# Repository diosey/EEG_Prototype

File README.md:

# EEG Prototype — Wireless Brain Activity Acquisition System

A prototype electroencephalograph (EEG) for acquiring and recording the brain's electrical activity, with real-time visualization in both time and frequency domains.

Developed as a degree project at Universidad Politécnica Territorial de Aragua "Federico Brito Figueroa" (Venezuela).

---

## Overview

This project implements a complete EEG acquisition system composed of:

- **Analog front-end**: Low-noise biopotential acquisition circuit with instrumentation amplifier, eighth-order active filter with butterworth topology, non-inverting adder for an offset to adapt the signal to logical level required for ADC and microcontroller, notch filter to mitigate the 60Hz noise 
- **Digital processing**: ESP32 microcontroller with websockets for communication
- **Wireless communication**: WiFi for real-time data streaming
- **Web interface**: Browser-based visualization of EEG signals in time and frequency domains with FIR and IIR digital filters

The system captures brain electrical activity on the ESP32, streams raw 16-bit samples over WebSocket, and applies digital filtering (31-tap FIR with Hamming window, 1st-order IIR, both low-pass and high-pass) in the browser for real-time visualization in the time and frequency domains.

---

## Specifications

| Parameter | Value |
|-----------|-------|
| Signal type | Brain electrical activity (EEG) |
| Channels | 1 |
|Biopotential amplifier | G = 10000 |
| Sampling rate | 430 Hz |
| ADC resolution | 16 bits |
| Microcontroller | ESP32 |
| Digital filters | FIR (31-tap, Hamming) + IIR (1st order) |
| Filter types | Low-pass and high-pass |
| Frequency analysis | Power spectrum (FFT) |
| Communication | WiFi (802.11 b/g/n) |
| Visualization | Web browser (HTML/JavaScript) |
| Firmware language | C |
| Design tool | KiCad |

---

## Design Highlights

- **Analog biopotential amplification**: Circuit based on the AD620 due to its low noise and high CMRR
- **Complete system integration**: Analog acquisition + digital processing + wireless communication + web visualization in a single project.
- **Digital signal processing**: FIR and IIR filters implemented in JavaScript on the client-side, with configurable low-pass and high-pass modes.
- **Frequency-domain analysis**: Real-time power spectrum computed via FFT.
- **Wireless data streaming**: WiFi WebSocket server streams EEG data to any browser.
- **Cross-platform visualization**: Works on PC, tablet, or smartphone without installing any application.
- **Open hardware design**: Full KiCad schematic, PCB, and Gerbers included.

---

## Repository Structure

- `hardware/` — KiCad schematic, PCB, Gerbers, BOM
- `firmware/` — ESP-IDF source project
- `docs/` — Design documentation, calculations, thesis summary

---

## Signal Processing

### FIR Filter
- **Topology**: 31-tap FIR
- **Window**: Hamming
- **Configurations**: Low-pass and high-pass

### IIR Filter
- **Topology**: 1st-order IIR
- **Configurations**: Low-pass and high-pass

### Frequency Analysis
- FFT-based power spectrum
- Real-time display in web interface

---

## Web Interface

The web interface allows visualization of EEG signals from any device with a browser (PC, tablet, smartphone) connected to the same WiFi network.

Features:
- Real-time time-domain plot
- Real-time frequency-domain plot (power spectrum)
- Filter selection (FIR/IIR, LP/HP)

---

## Tools Used

- **KiCad** — Schematic capture, PCB layout
- **ESP-IDF / PlatformIO** — ESP32 firmware development
- **C** — Firmware programming language
- **HTML/CSS/JavaScript** — Web interface

---

## Team

- **David Obregon** 
- **Diosey Lugo** 

**Tutor:** Prof. Carlos Aponte

**Institution:** Universidad Politécnica Territorial de Aragua "Federico Brito Figueroa"
**Date:** April 2026

---

## Author Contact
- **Gmail:** dioseyadolfolugo@gmail.com
- **GitHub:** https://github.com/diosey
- **LinkedIn:** http://www.linkedin.com/in/adolfodiaz01

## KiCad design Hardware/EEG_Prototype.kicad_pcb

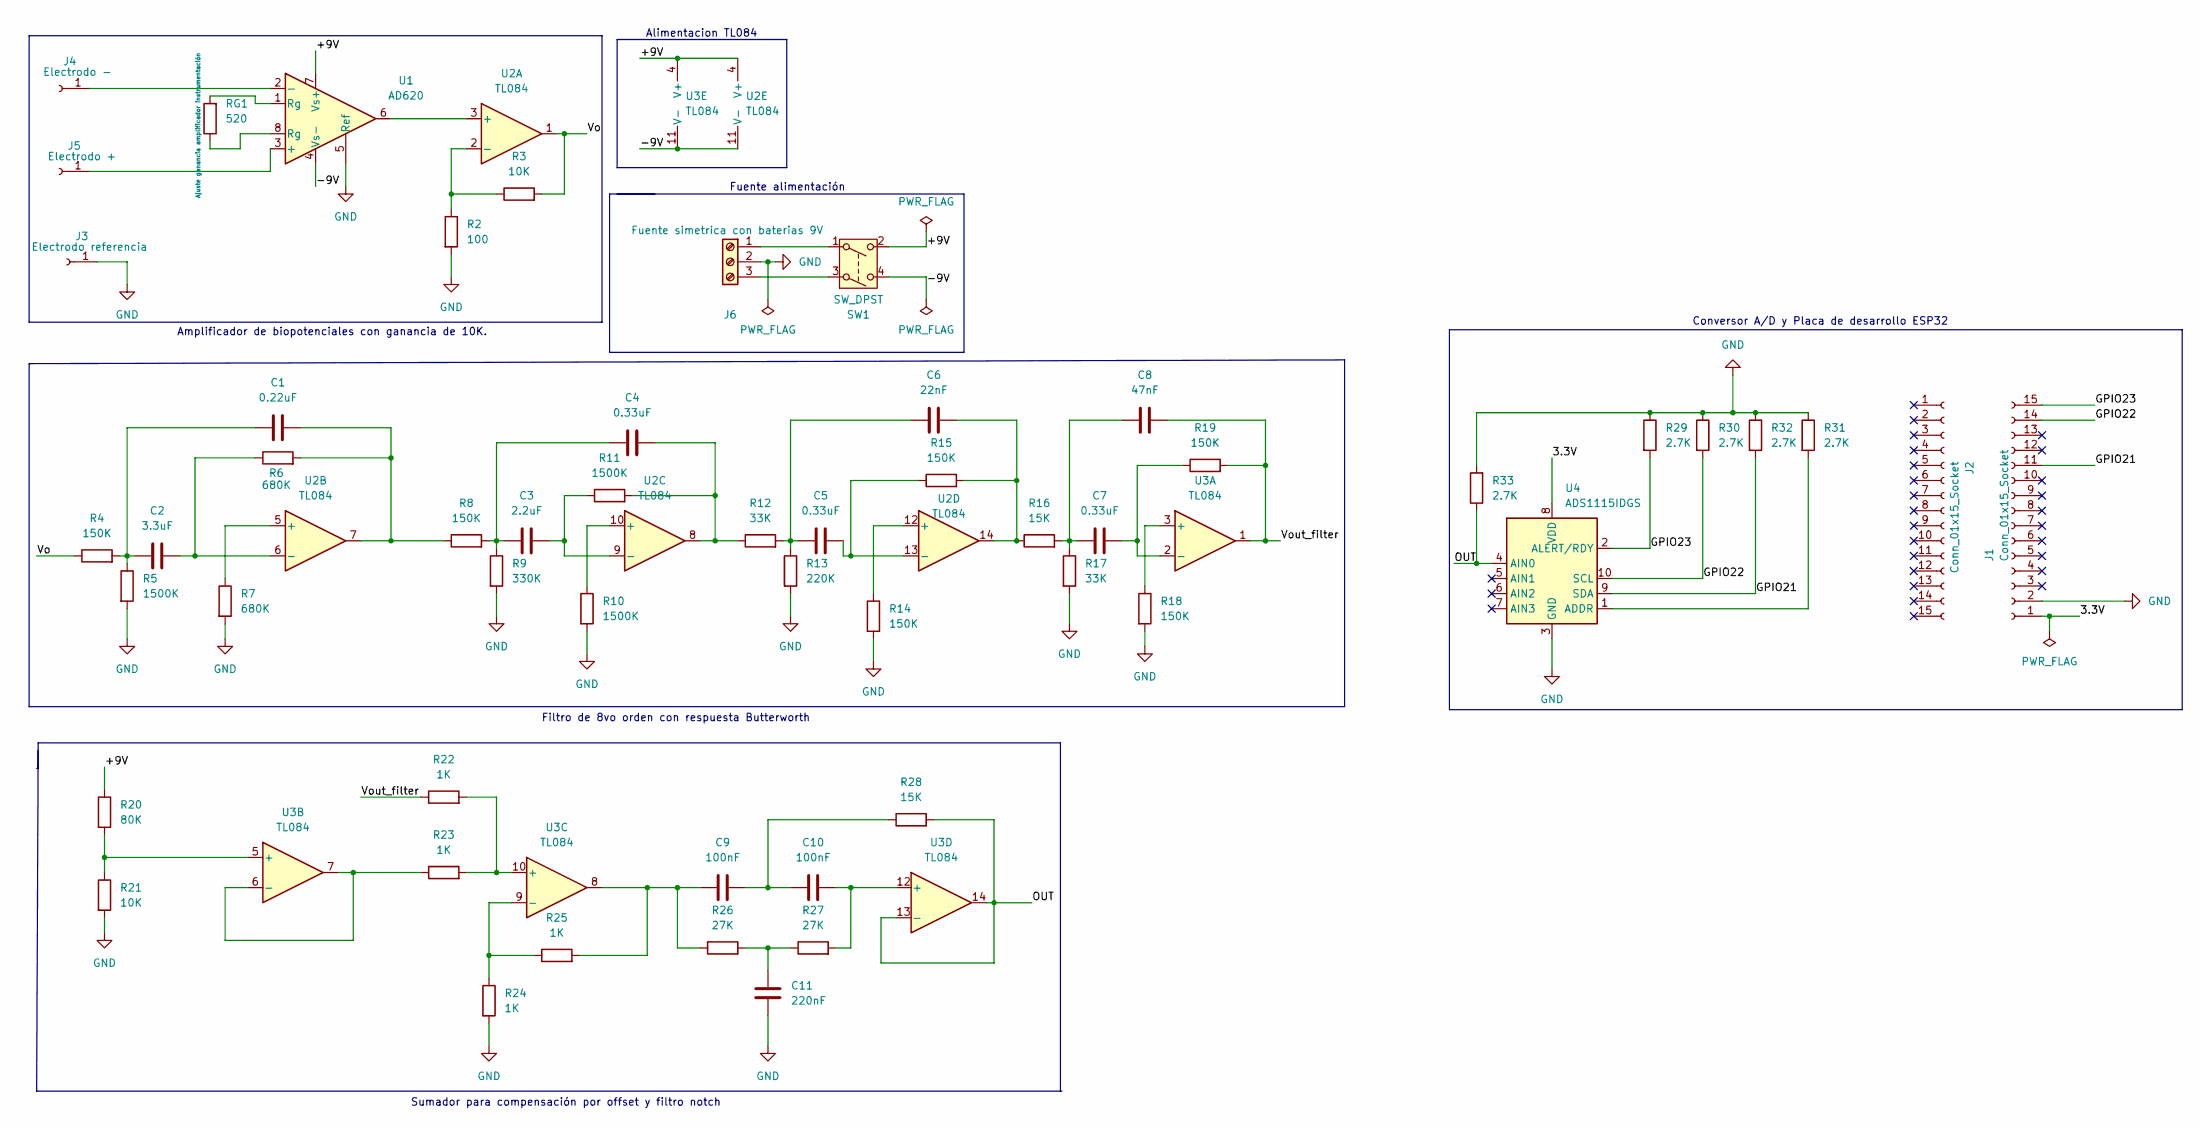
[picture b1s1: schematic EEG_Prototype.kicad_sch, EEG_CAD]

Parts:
C1: 0.22uF; C_Disc_D4.7mm_W2.5mm_P5.00mm
C2: 3.3uF; C_Radial_D5.0mm_H7.0mm_P2.00mm
C3: 2.2uF; C_Radial_D5.0mm_H7.0mm_P2.00mm
C4, C5, C7: 0.33uF; C_Disc_D4.7mm_W2.5mm_P5.00mm
C6: 22nF; C_Disc_D4.7mm_W2.5mm_P5.00mm
C8: 47nF; C_Disc_D4.7mm_W2.5mm_P5.00mm
C9, C10: 100nF; C_Disc_D4.7mm_W2.5mm_P5.00mm
C11: 220nF; C_Disc_D4.7mm_W2.5mm_P5.00mm
J1, J2: Conn_01x15_Socket; PinSocket_1x15_P2.54mm_Vertical
J3: Conn_01x01_Socket; Banana_Cliff_FCR7350N_S16N-PC_Horizontal
J4: Conn_01x01_Socket; Banana_Cliff_FCR7350B_S16N-PC_Horizontal
J5: Conn_01x01_Socket; Banana_Cliff_FCR7350R_S16N-PC_Horizontal
J6: Screw_Terminal_01x03; TerminalBlock_Phoenix_MPT-0,5-3-2.54_1x03_P2.54mm_Horizontal
R2: 100; R_Axial_DIN0204_L3.6mm_D1.6mm_P5.08mm_Horizontal
R3, R21: 10K; R_Axial_DIN0204_L3.6mm_D1.6mm_P5.08mm_Horizontal
R4, R8, R14, R15, R18, R19: 150K; R_Axial_DIN0204_L3.6mm_D1.6mm_P5.08mm_Horizontal
R5, R10, R11: 1500K; R_Axial_DIN0204_L3.6mm_D1.6mm_P5.08mm_Horizontal
R6, R7: 680K; R_Axial_DIN0204_L3.6mm_D1.6mm_P5.08mm_Horizontal
R9: 330K; R_Axial_DIN0204_L3.6mm_D1.6mm_P5.08mm_Horizontal
R12, R17: 33K; R_Axial_DIN0204_L3.6mm_D1.6mm_P5.08mm_Horizontal
R13: 220K; R_Axial_DIN0204_L3.6mm_D1.6mm_P5.08mm_Horizontal
R16, R28: 15K; R_Axial_DIN0204_L3.6mm_D1.6mm_P5.08mm_Horizontal
R20: 80K; R_Axial_DIN0204_L3.6mm_D1.6mm_P5.08mm_Horizontal
R22, R23, R24, R25: 1K; R_Axial_DIN0204_L3.6mm_D1.6mm_P5.08mm_Horizontal
R26, R27: 27K; R_Axial_DIN0204_L3.6mm_D1.6mm_P5.08mm_Horizontal
R29, R30, R31, R32, R33: 2.7K; R_Axial_DIN0204_L3.6mm_D1.6mm_P5.08mm_Horizontal
RG1: 520; R_Axial_DIN0204_L3.6mm_D1.6mm_P5.08mm_Horizontal
SW1: SW_DPST; SW_DIP_SPSTx02_Slide_9.78x7.26mm_W7.62mm_P2.54mm
U1: AD620; DIP-8_W7.62mm_Socket
U2, U3: TL084; DIP-14_W7.62mm_Socket
U4: ADS1115IDGS; TSSOP-10_3x3mm_P0.5mm

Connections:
/3.3V: J1.1, U4.8 (VDD)
/+9V: R20.1, SW1.2, U1.7 (Vs+), U2.4 (V+), U3.4 (V+)
/-9V: SW1.4, U1.4 (Vs-), U2.11 (V-), U3.11 (V-)
/GPIO21: J1.11, R32.2, U4.9 (SDA)
/GPIO22: J1.14, R30.2, U4.10 (SCL)
/GPIO23: J1.15, R29.2, U4.2 (ALERT/RDY)
/OUT: R28.2, R33.1, U3.13 (-), U3.14, U4.4 (AIN0)
/Vo: R3.2, R4.1, U2.1
/Vout_filter: C8.2, R19.2, R22.1, U3.1
GND: C11.1, J1.2, J3.1, J6.2, R2.2, R5.2, R7.2, R9.2, R10.2, R13.2, R14.2, R17.2, R18.2, R21.2, R24.2, R29.1, R30.1, R31.1, R32.1, R33.2, U1.5 (Ref), U4.3 (GND)
unnamed: C1.1, C2.1, R4.2, R5.1
unnamed: C1.2, R6.2, R8.1, U2.7
unnamed: C3.1, C4.1, R8.2, R9.1
unnamed: C4.2, R11.2, R12.1, U2.8
unnamed: C5.1, C6.1, R12.2, R13.1
unnamed: C6.2, R15.2, R16.1, U2.14
unnamed: C7.1, C8.1, R16.2, R17.1
unnamed: C9.1, R25.2, R26.1, U3.8
unnamed: C9.2, C10.1, R28.1
unnamed: C11.2, R26.2, R27.1
unnamed: J4.1, U1.2 (-)
unnamed: J5.1, U1.3 (+)
unnamed: J6.1, SW1.1
unnamed: J6.3, SW1.3
unnamed: RG1.1, U1.8 (Rg)
unnamed: RG1.2, U1.1 (Rg)
unnamed: U1.6, U2.3 (+)
unnamed: R2.1, R3.1, U2.2 (-)
unnamed: R7.1, U2.5 (+)
unnamed: C2.2, R6.1, U2.6 (-)
unnamed: R10.1, U2.10 (+)
unnamed: C3.2, R11.1, U2.9 (-)
unnamed: R14.1, U2.12 (+)
unnamed: C5.2, R15.1, U2.13 (-)
unnamed: R18.1, U3.3 (+)
unnamed: C7.2, R19.1, U3.2 (-)
unnamed: R20.2, R21.1, U3.5 (+)
unnamed: R23.1, U3.6 (-), U3.7
unnamed: R22.2, R23.2, U3.10 (+)
unnamed: R24.1, R25.1, U3.9 (-)
unnamed: C10.2, R27.2, U3.12 (+)
unnamed: R31.2, U4.1 (ADDR)

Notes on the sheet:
Sumador para compensación por offset y filtro notch
Filtro de 8vo orden con respuesta Butterworth
Conversor A/D y Placa de desarrollo ESP32
Amplificador de biopotenciales con ganancia de 10K.
Fuente alimentación
Alimentacion TL084

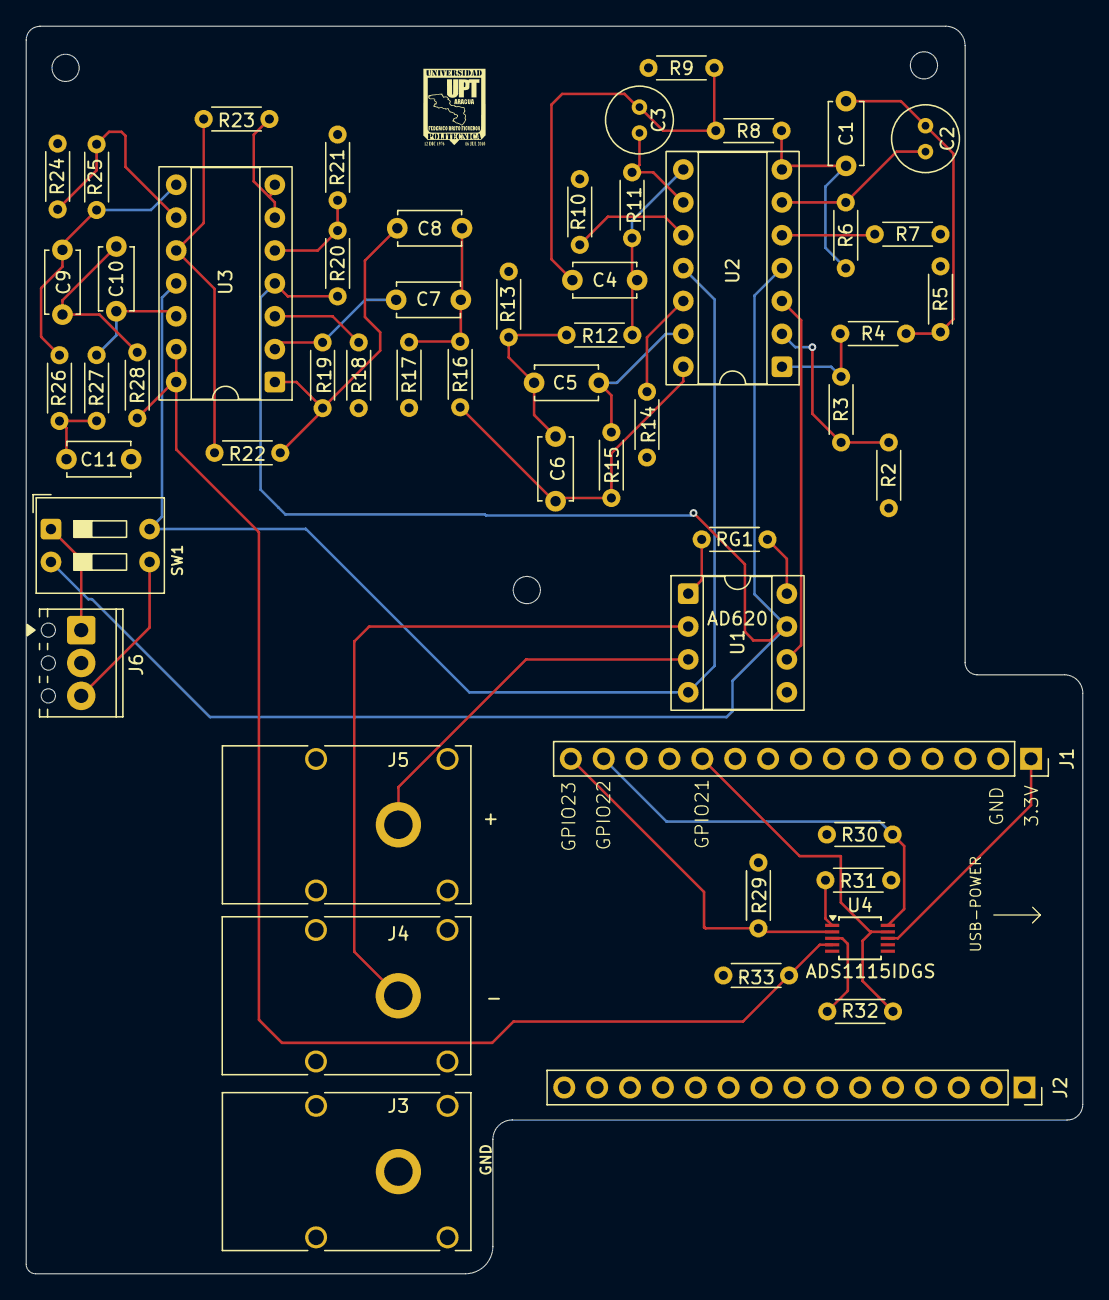
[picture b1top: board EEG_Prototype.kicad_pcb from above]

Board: 2 copper layers, 81.6 x 96.4 mm, 55 parts (0 on the bottom side), 42 nets.
